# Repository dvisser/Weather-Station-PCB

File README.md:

# Weather-Station-PCB

A PCB designed in KiCAD to accurately monitor the weather using a variety of sensors and instrumentation.

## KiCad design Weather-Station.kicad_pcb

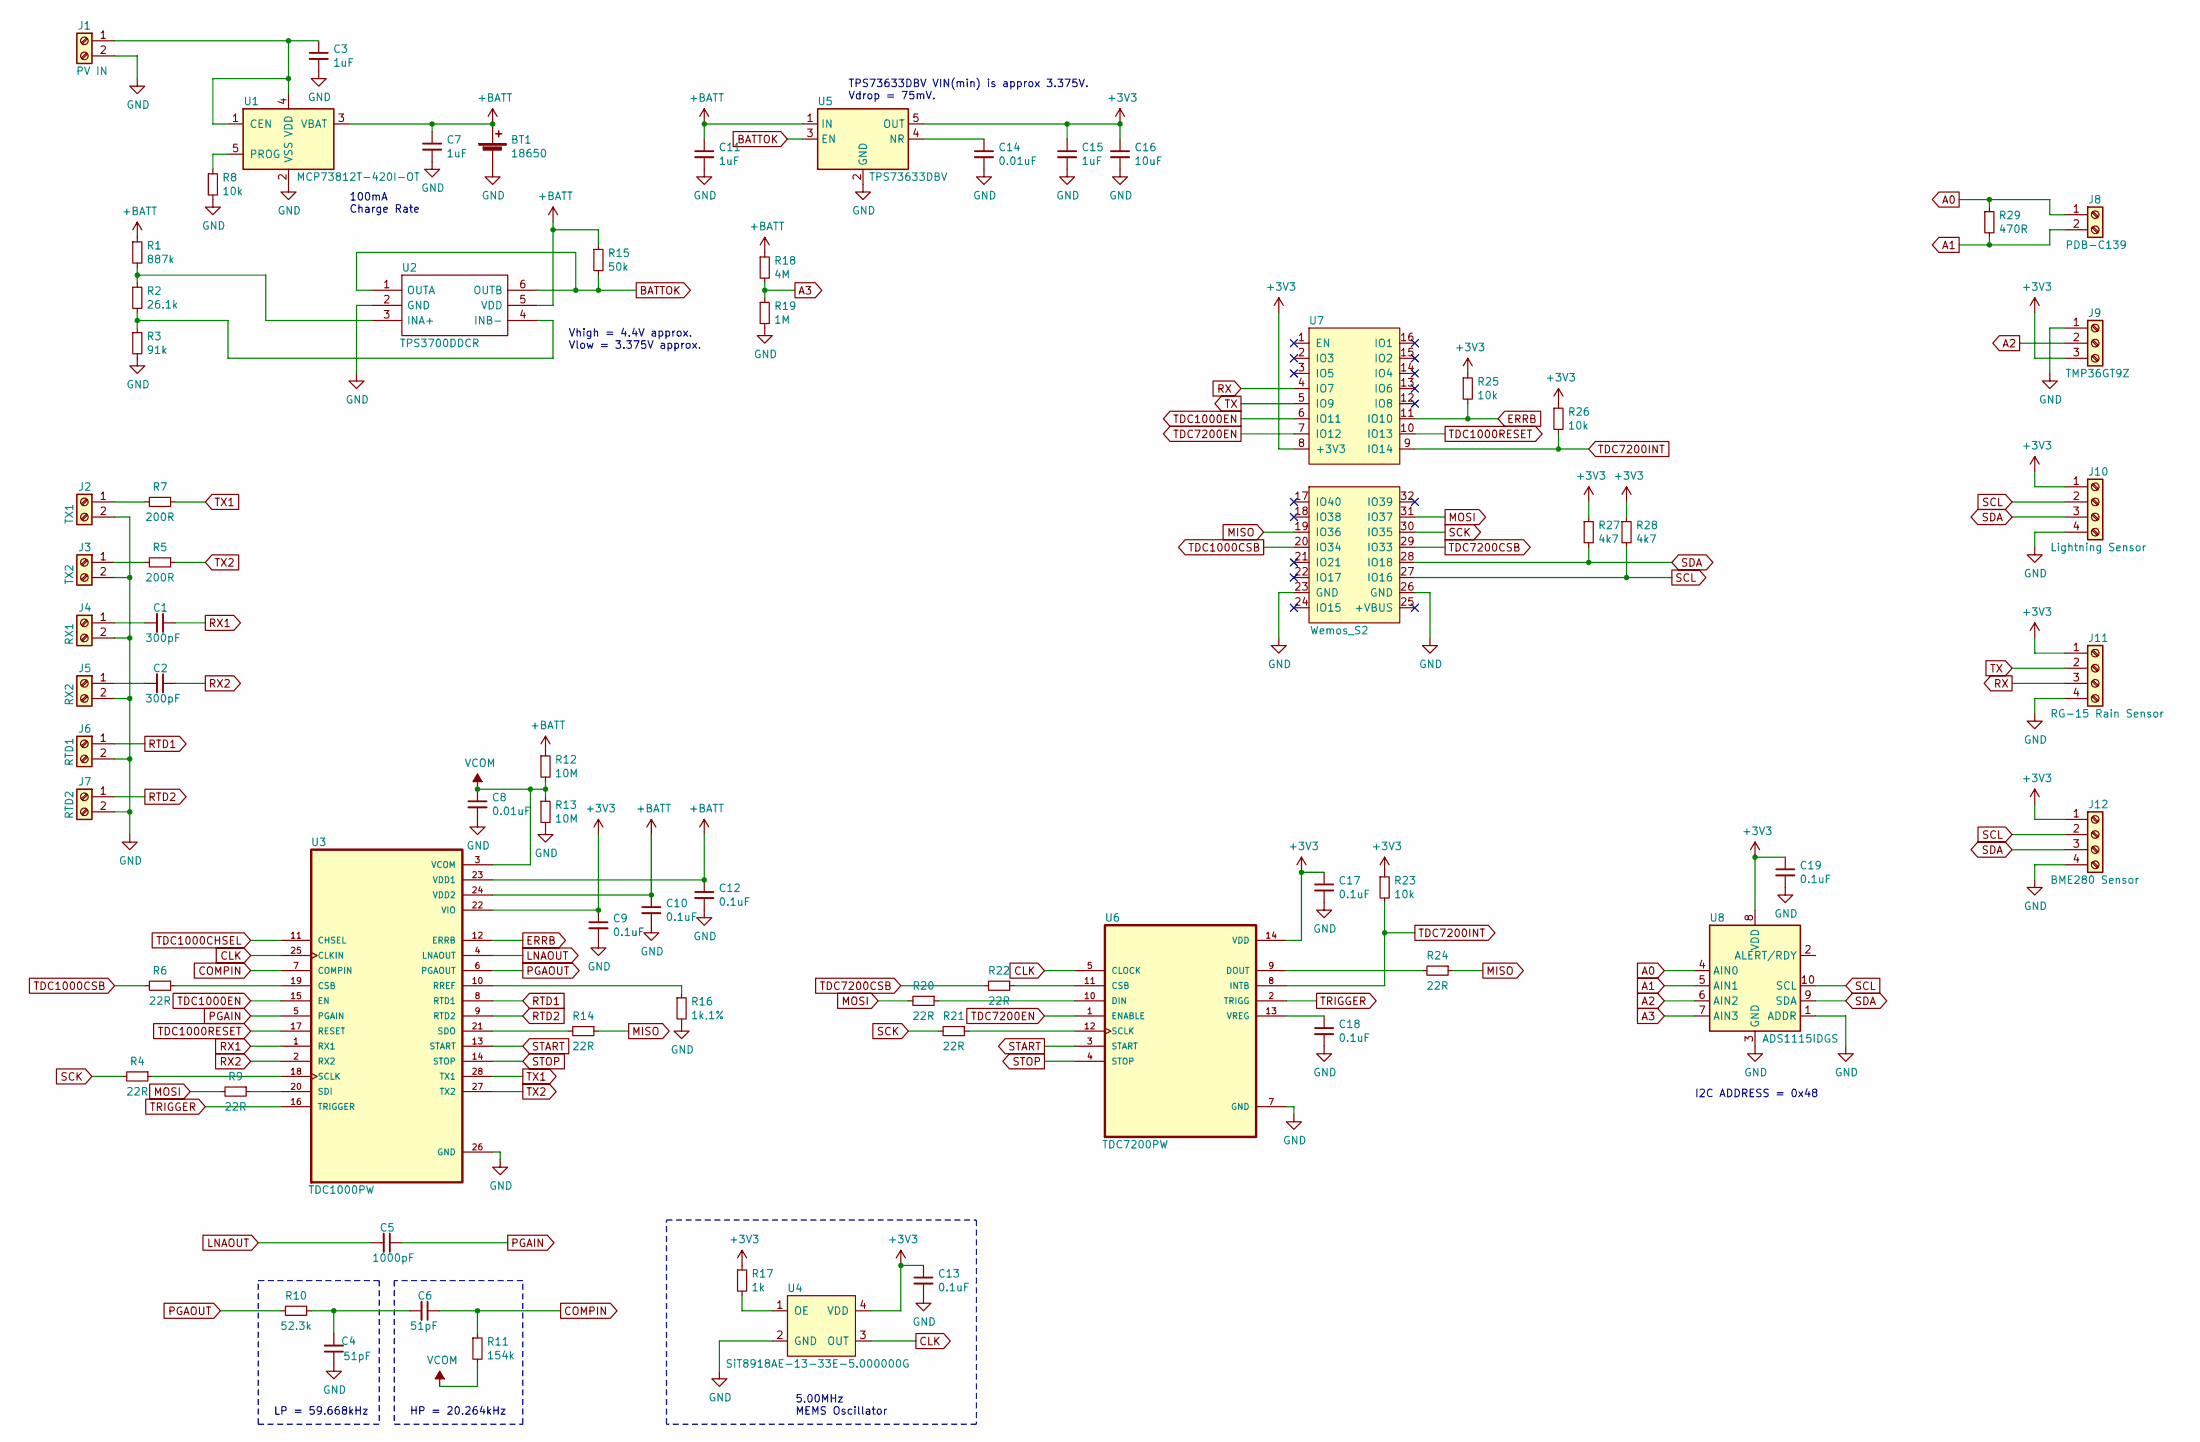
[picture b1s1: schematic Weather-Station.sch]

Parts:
BT1: 18650; BatteryHolder_Keystone_1042_1x18650
C1, C2: 300pF; C_0805_2012Metric
C3, C7, C11, C15: 1uF; C_0805_2012Metric
C4, C6: 51pF; C_0805_2012Metric
C5: 1000pF; C_0805_2012Metric
C8, C14: 0.01uF; C_0805_2012Metric
C9, C10, C12, C13, C17, C18, C19: 0.1uF; C_0805_2012Metric
C16: 10uF; C_0805_2012Metric
J1: PV IN; TerminalBlock_bornier-2_P5.08mm
J2: TX1; TerminalBlock_bornier-2_P5.08mm
J3: TX2; TerminalBlock_bornier-2_P5.08mm
J4: RX1; TerminalBlock_bornier-2_P5.08mm
J5: RX2; TerminalBlock_bornier-2_P5.08mm
J6: RTD1; TerminalBlock_bornier-2_P5.08mm
J7: RTD2; TerminalBlock_bornier-2_P5.08mm
J8: PDB-C139; TerminalBlock_bornier-2_P5.08mm
J9: TMP36GT9Z; TerminalBlock_bornier-3_P5.08mm
J10: Lightning Sensor; TerminalBlock_bornier-4_P5.08mm
J11: RG-15 Rain Sensor; TerminalBlock_bornier-4_P5.08mm
J12: BME280 Sensor; TerminalBlock_bornier-4_P5.08mm
R1: 887k; R_0805_2012Metric
R2: 26.1k; R_0805_2012Metric
R3: 91k; R_0805_2012Metric
R4, R6, R9, R14, R20, R21, R22, R24: 22R; R_0805_2012Metric
R5, R7: 200R; R_0805_2012Metric
R8, R23, R25, R26: 10k; R_0805_2012Metric
R10: 52.3k; R_0805_2012Metric
R11: 154k; R_0805_2012Metric
R12, R13: 10M; R_0805_2012Metric
R15: 50k; R_0805_2012Metric
R16: 1k,1%; R_0805_2012Metric
R17: 1k; R_0805_2012Metric
R18: 4M; R_0805_2012Metric
R19: 1M; R_0805_2012Metric
R27, R28: 4k7; R_0805_2012Metric
R29: 470R; R_0805_2012Metric
U1: MCP73812T-420I-OT; SOT-23-5
U2: TPS3700DDCR; TSOT-23-6; Manufacturer_Part_Number TPS3700DDCR; Mouser Part Number 595-TPS3700DDCR
U3: TDC1000PW; SOP65P640X120-28N
U4: SiT8918AE-13-33E-5.000000G; Oscillator_SMD_Abracon_ASDMB-4Pin_2.5x2.0mm
U5: TPS73633DBV; SOT-23-5
U6: TDC7200PW; SOP65P640X120-14N
U7: Wemos_S2; WEMOS_S2
U8: ADS1115IDGS; TSSOP-10_3x3mm_P0.5mm

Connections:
+3V3: C9.1, C13.1, C15.1, C16.1, C17.1, C19.1, J9.3, J10.1, J11.1, J12.1, R17.1, R23.1, R25.1, R26.1, R27.1, R28.1, U3.22 (VIO), U4.4 (VDD), U5.5 (OUT), U6.14 (VDD), U7.8 (+3V3), U8.8 (VDD)
+BATT: BT1.1 (+), C7.1, C10.1, C11.1, C12.1, R1.1, R12.1, R15.1, R18.1, U1.3 (VBAT), U2.5 (VDD), U3.23 (VDD1), U3.24 (VDD2), U5.1 (IN)
A0: J8.1, R29.1, U8.4 (AIN0)
A1: J8.2, R29.2, U8.5 (AIN1)
A2: J9.2, U8.6 (AIN2)
A3: R18.2, R19.1, U8.7 (AIN3)
BATTOK: R15.2, U2.1 (OUTA), U2.6 (OUTB), U5.3 (EN); also elsewhere on the board
CLK: U3.25 (CLKIN), U4.3 (OUT), U6.5 (CLOCK); also elsewhere on the board
COMPIN: C6.1, R11.1, U3.7 (COMPIN)
ERRB: R25.2, U3.12 (ERRB), U7.11 (IO10)
GND: BT1.2 (-), C3.2, C4.1, C7.2, C8.2, C9.2, C10.2, C11.2, C12.2, C13.2, C14.2, C15.2, C16.2, C17.2, C18.2, C19.2, J1.2, J2.2, J3.2, J4.2, J5.2, J6.2, J7.2, J9.1, J10.4, J11.4, J12.4, R3.2, R8.2, R13.2, R16.2, R19.2, U1.2 (VSS), U2.2 (GND), U3.26 (GND), U4.2 (GND), U5.2 (GND), U6.7 (GND), U7.23 (GND), U7.26 (GND), U8.1 (ADDR), U8.3 (GND)
LNAOUT: C5.2, U3.4 (LNAOUT)
MISO: R14.1, R24.1, U7.19 (IO36)
MOSI: R9.2, R20.2, U7.31 (IO37)
unnamed: C1.2, J4.1
unnamed: C2.2, J5.1
unnamed: C3.1, J1.1, U1.1 (CEN), U1.4 (VDD)
unnamed: C4.2, C6.2, R10.1
unnamed: C14.1, U5.4 (NR)
unnamed: C18.1, U6.13 (VREG)
unnamed: J2.1, R7.2
unnamed: J3.1, R5.2
unnamed: R1.2, R2.1, U2.3 (INA+)
unnamed: R2.2, R3.1, U2.4 (INB-)
unnamed: R4.1, U3.18 (SCLK)
unnamed: R6.1, U3.19 (CSB)
unnamed: R8.1, U1.5 (PROG)
unnamed: R9.1, U3.20 (SDI)
unnamed: R14.2, U3.21 (SDO)
unnamed: R16.1, U3.10 (RREF)
unnamed: R17.2, U4.1 (OE)
unnamed: R20.1, U6.10 (DIN)
unnamed: R21.1, U6.12 (SCLK)
unnamed: R22.1, U6.11 (CSB)
unnamed: R24.2, U6.9 (DOUT)
PGAIN: C5.1, U3.5 (PGAIN)
PGAOUT: R10.2, U3.6 (PGAOUT)
RTD1: J6.1, U3.8 (RTD1)
RTD2: J7.1, U3.9 (RTD2)
RX: J11.3, U7.4 (IO7)
RX1: C1.1, U3.1 (RX1)
RX2: C2.1, U3.2 (RX2)
SCK: R4.2, R21.2, U7.30 (IO35)
SCL: J10.2, J12.2, R28.2, U7.27 (IO16), U8.10 (SCL)
SDA: J10.3, J12.3, R27.2, U7.28 (IO18), U8.9 (SDA)
START: U3.13 (START), U6.3 (START)
STOP: U3.14 (STOP), U6.4 (STOP)
TDC1000CHSEL: U3.11 (CHSEL), U7.32 (IO39)
TDC1000CSB: R6.2, U7.20 (IO34)
TDC1000EN: U3.15 (EN), U7.6 (IO11)
TDC1000RESET: U3.17 (RESET), U7.10 (IO13)
TDC7200CSB: R22.2, U7.29 (IO33)
TDC7200EN: U6.1 (ENABLE), U7.7 (IO12)
TDC7200INT: R23.2, R26.2, U6.8 (INTB), U7.9 (IO14)
TRIGGER: U3.16 (TRIGGER), U6.2 (TRIGG)
TX: J11.2, U7.5 (IO9)
TX1: R7.1, U3.28 (TX1)
TX2: R5.1, U3.27 (TX2)
VCOM: C8.1, R11.2, R12.2, R13.1, U3.3 (VCOM)

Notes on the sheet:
LP = 59.668kHz
HP = 20.264kHz
100mA Charge Rate
5.00MHz MEMS Oscillator
TPS73633DBV VIN(min) is approx 3.375V. Vdrop = 75mV.
Vhigh = 4.4V approx. Vlow = 3.375V approx.
I2C ADDRESS = 0x48

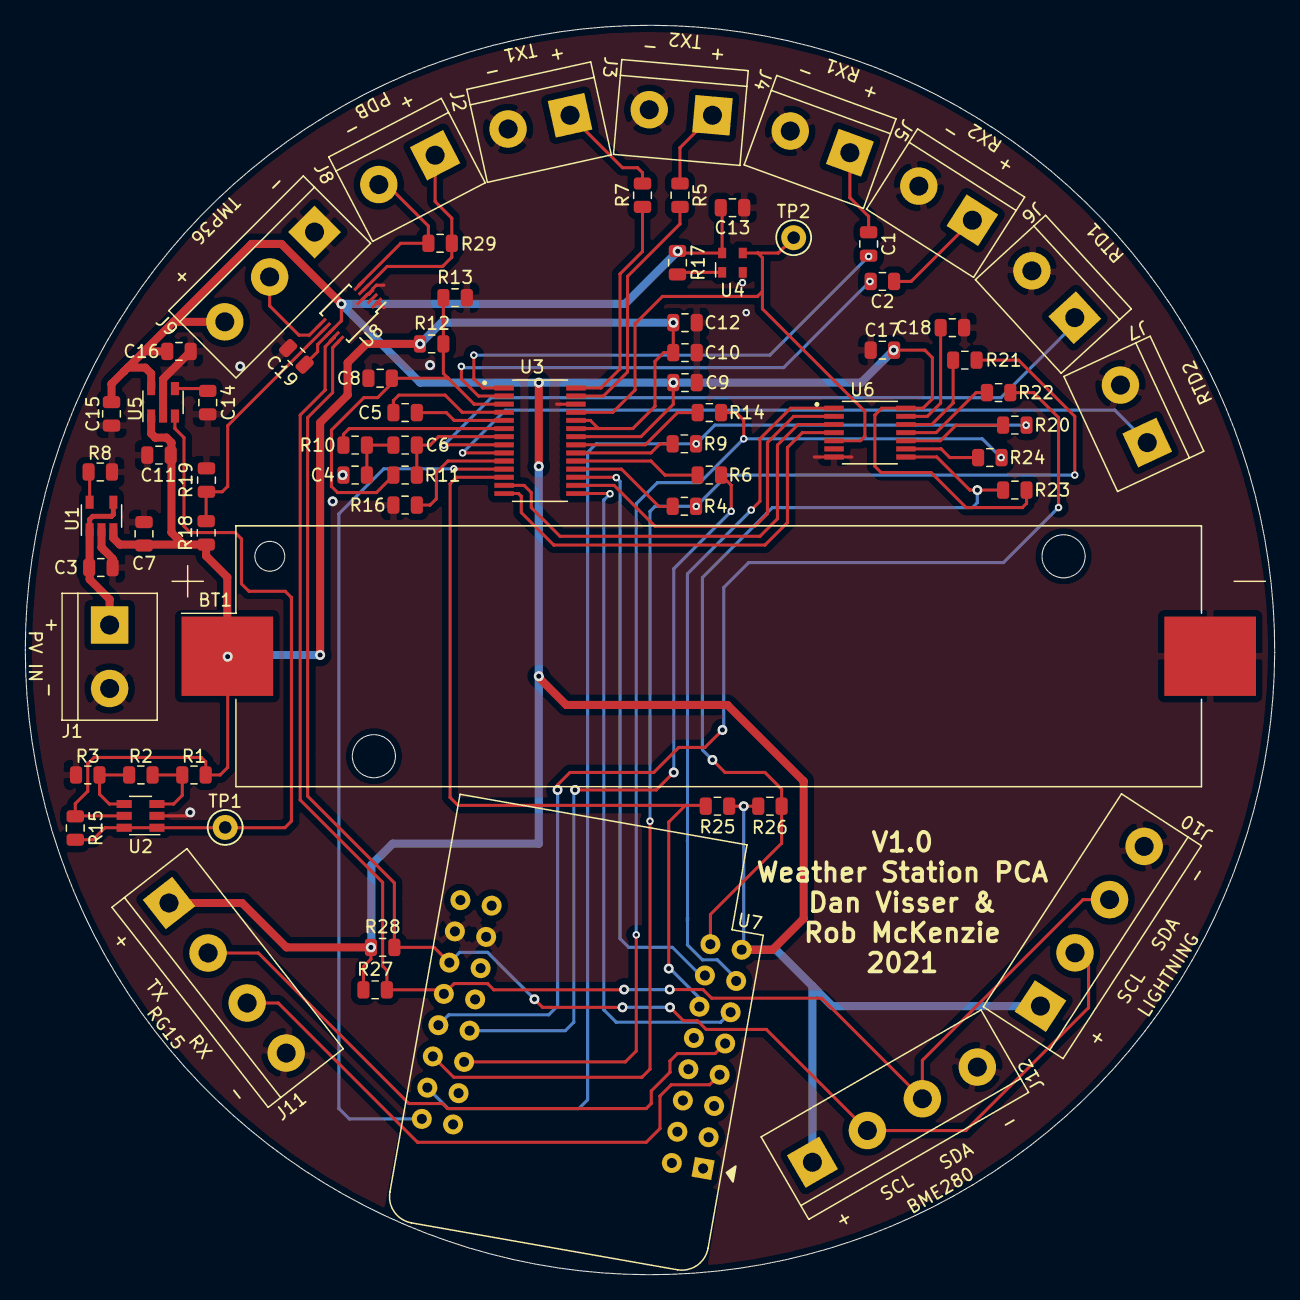
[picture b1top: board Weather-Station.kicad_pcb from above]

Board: 2 copper layers, 100.0 x 100.0 mm, 71 parts (0 on the bottom side), 59 nets.

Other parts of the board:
TP1, TP2: TestPoint; TestPoint_Keystone_5000-5004_Miniature

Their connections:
BATTOK: TP1.1; also elsewhere on the board
CLK: TP2.1; also elsewhere on the board

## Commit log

2021-10-22 Create LICENSE
2021-10-23 Initial in-progress commit.....
2021-10-28 more in-progress work.....
2021-10-29 more work.......
2021-10-29 more work
2021-11-12 Added VBAT monitor
    added vbat monitor and changed vreg to low dropout type
2021-11-12 Add lightning sensor interface
2021-11-25 Added 3.3V TTL for rain gauge and start of photoelectric circuit
2021-12-01 added sensor interfaces
2021-12-03 Finished schematic
2021-12-03 Annotate schematic
2021-12-03 Add schematic PDF
2021-12-03 Added pullups to ERRB & TDC2000INT, screw terminals for sensors.
2021-12-03 Start of PCB layout
2021-12-03 Continued board layout
2021-12-06 more pcb layout
2021-12-07 PCB component placement complete.
2021-12-07 Updated PDF schematic
2021-12-07 to be continued
2021-12-08 pcb routing work continues
2021-12-08 Routing completed.
2021-12-08 Fixed keepout under ESP32-S2 antenna.
2021-12-11 Added version, name and author text.
2021-12-14 Minor graphic changes, artwork complete.
2021-12-14 Gerber and Drill File v1.0 Release
2021-12-23 Generate STP file of PCB
